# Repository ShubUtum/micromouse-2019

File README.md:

TODOs:

- [x] write a gitignore file
- [x] Timer Interrupt
- [x] PWM
- [x] UART TX, USB interface
- [x] Motor driver, H-Bridge interface
- [x] Motor Encoder 
- [x] PWM fix
- [x] ADC
- [ ] UART RX
- [ ] Schematic, routing
- [ ] PID controller
- [ ] moveing forward alignment & correction
- [ ] rotate left & right based on the POSCNT
- [ ] Map generation (maze discovery)
- [ ] finding shortest path to goal

- [ ] LED for measuring execution time
- [ ] UART, BT interface
- [ ] Visualization of UART data

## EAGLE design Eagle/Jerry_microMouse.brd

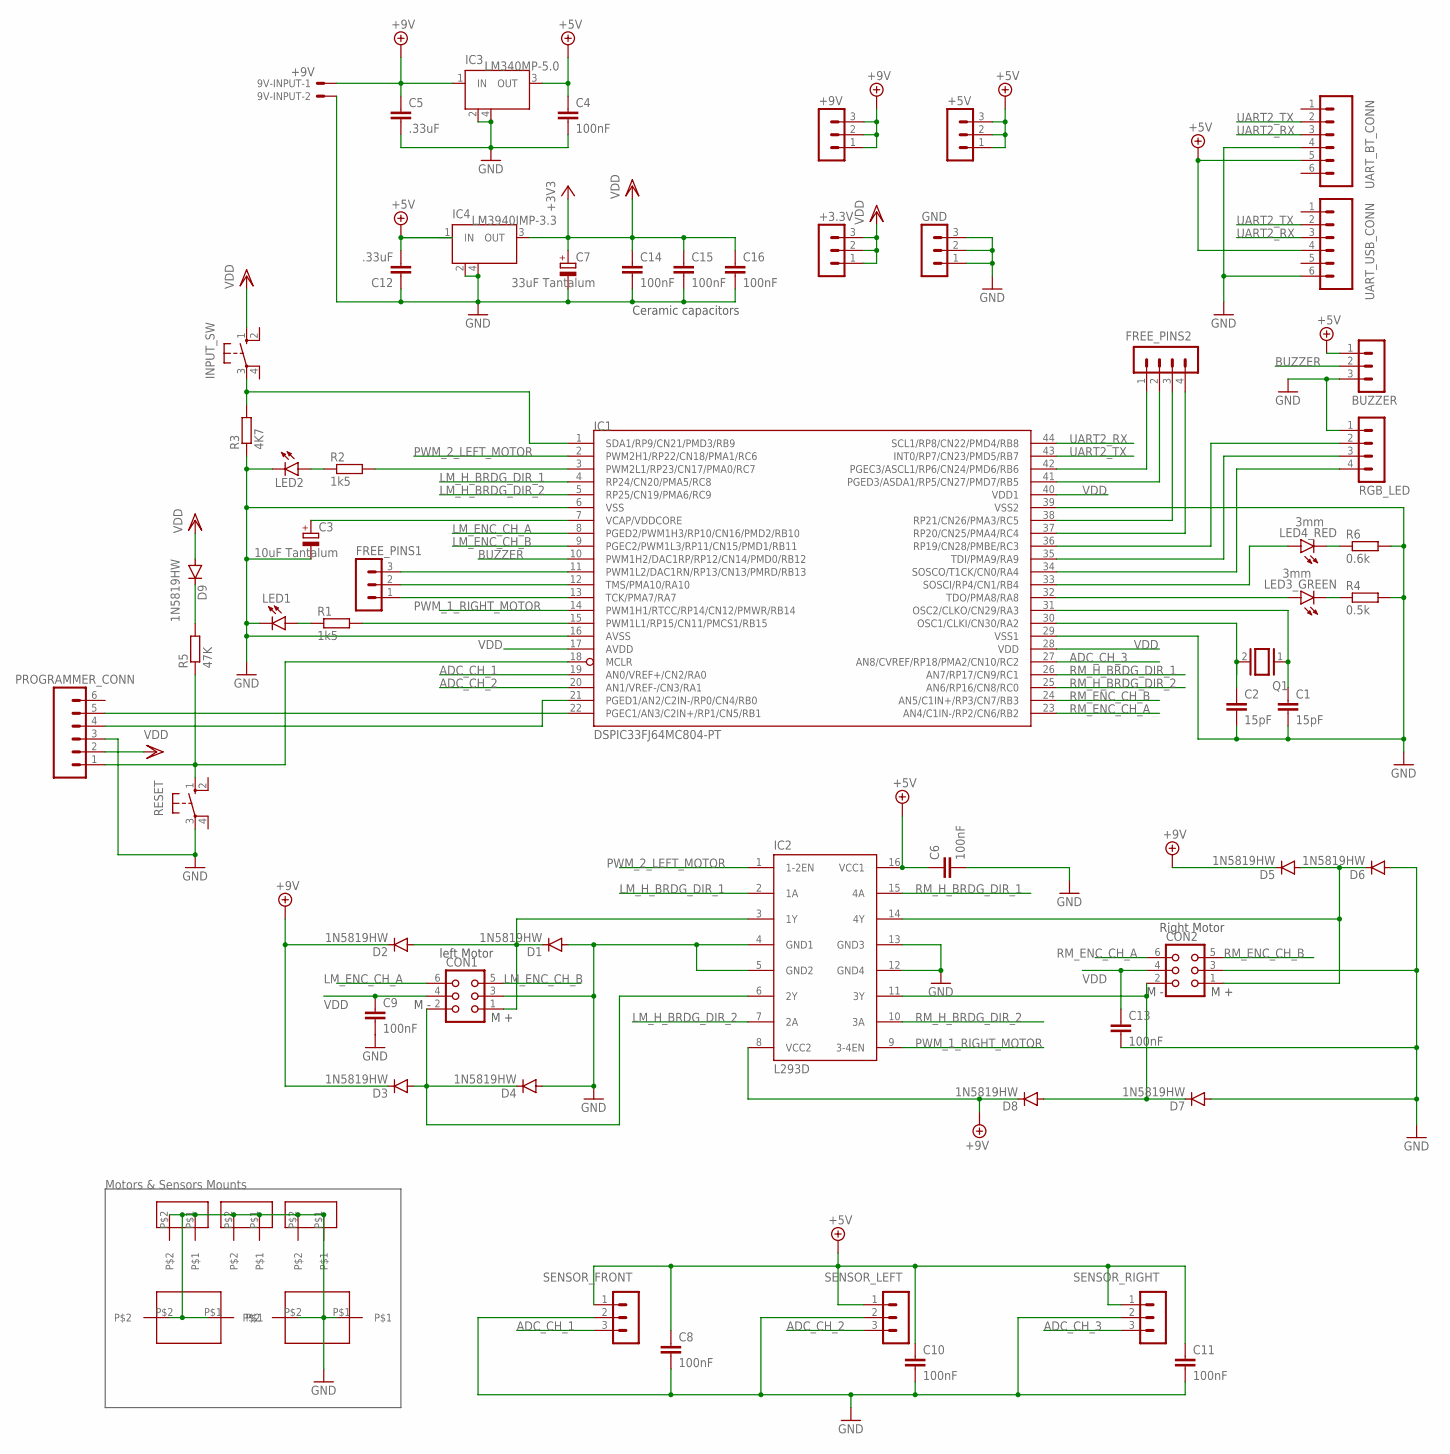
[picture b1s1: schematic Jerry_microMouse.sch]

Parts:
9V-INPUT: +9V; 22-23-2021
+3.3V, +5V, +9V: MA03-1
BUZZER: MA03-1
C1, C2: 15pF; C0805
C3: 10uF Tantalum; CT3216
C4, C6, C8, C9, C10, C11, C13, C14, C15, C16: 100nF; C0805
C5, C12: .33uF; C0805
C7: 33uF Tantalum; CT7343
CON1, CON2: CON06L
D1, D2, D3, D4, D5, D6, D7, D8, D9: 1N5819HW; SOD-123_MINI-SMA
FREE_PINS1: MA03-1
FREE_PINS2: MA04-1
GND: MA03-1
IC1: DSPIC33FJ64MC804-PT; TQFP44
IC2: L293D; DIL16
IC3: LM340MP-5.0; SOT223
IC4: LM3940IMP-3.3; SOT223
INPUT_SW: 10-XX; B3F-10XX
LED1, LED2: LED5MM
LED3_GREEN, LED4_RED: 3mm; Q62902-B155
PROGRAMMER_CONN: M06; 06P
Q1: XTAL/S; QS
R1, R2: 1k5; R0805
R3: 4K7; R0805
R4: 0.5k; R0805
R5: 47K; R0805
R6: 0.6k; R0805
RESET: 10-XX; B3F-10XX
RGB_LED: MA04-1
SENSOR_FRONT: MA03-1
SENSOR_LEFT: MA03-1
SENSOR_RIGHT: MA03-1
SENS_MNT_F: SENSOR_MOUNT_F; SENSOR_MOUNT
SENS_MNT_L: SENSOR_MOUNT_L; SENSOR_MOUNT
SENS_MNT_R: SENSOR_MOUNT_R; SENSOR_MOUNT
U$1, U$2: MOTOR_MOUNT
UART_BT_CONN: M06; 06P
UART_USB_CONN: M06; 06P

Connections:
+5V: +5V.1, +5V.2, +5V.3, BUZZER.1, C4.1, C6.1, C8.1, C10.1, C11.1, C12.2, IC2.16 (VCC1), IC3.3 (OUT), IC4.1 (IN), SENSOR_FRONT.1, SENSOR_LEFT.1, SENSOR_RIGHT.1, UART_BT_CONN.5, UART_USB_CONN.4
+9V: 9V-INPUT.1, +9V.1, +9V.2, +9V.3, C5.1, D2.C, D3.C, D5.C, D8.C, IC2.8 (VCC2), IC3.1 (IN)
ADC_CH_1: IC1.19 (AN0/VREF+/CN2/RA0), SENSOR_FRONT.3
ADC_CH_2: IC1.20 (AN1/VREF-/CN3/RA1), SENSOR_LEFT.3
ADC_CH_3: IC1.27 (AN8/CVREF/RP18/PMA2/CN10/RC2), SENSOR_RIGHT.3
BUZZER: BUZZER.2, IC1.10 (PWM1H2/DAC1RP/RP12/CN14/PMD0/RB12)
GND: 9V-INPUT.2, BUZZER.3, C1.2, C2.2, C3.-, C4.2, C5.2, C6.2, C7.-, C8.2, C9.2, C10.2, C11.2, C12.1, C13.2, C14.2, C15.2, C16.2, CON1.3, CON2.3, D1.A, D4.A, D6.A, D7.A, GND.1, GND.2, GND.3, IC1.6 (VSS), IC1.16 (AVSS), IC1.29 (VSS1), IC1.39 (VSS2), IC2.4 (GND1), IC2.5 (GND2), IC2.12 (GND4), IC2.13 (GND3), IC3.2 (GND), IC3.4 (GND), IC4.2 (GND), IC4.4 (GND), LED1.K (C), LED2.K (C), PROGRAMMER_CONN.3, R3.1, R4.2, R6.2, RESET.3, RGB_LED.1, SENSOR_FRONT.2, SENSOR_LEFT.2, SENSOR_RIGHT.2, SENS_MNT_F.P$1, SENS_MNT_F.P$2, SENS_MNT_L.P$1, SENS_MNT_L.P$2, SENS_MNT_R.P$1, SENS_MNT_R.P$2, U$1.P$1, U$1.P$2, U$2.P$1, U$2.P$2, UART_BT_CONN.4, UART_USB_CONN.6
LM_ENC_CH_A: CON1.6, IC1.8 (PGED2/PWM1H3/RP10/CN16/PMD2/RB10)
LM_ENC_CH_B: CON1.5, IC1.9 (PGEC2/PWM1L3/RP11/CN15/PMD1/RB11)
LM_H_BRDG_DIR_1: IC1.4 (RP24/CN20/PMA5/RC8), IC2.2 (1A)
LM_H_BRDG_DIR_2: IC1.5 (RP25/CN19/PMA6/RC9), IC2.7 (2A)
LM_M+: CON1.1, D1.C, D2.A, IC2.3 (1Y)
LM_M-: CON1.2, D3.A, D4.C, IC2.6 (2Y)
unnamed: IC1.3 (PWM2L1/RP23/CN17/PMA0/RC7), R2.2
unnamed: LED2.A, R2.1
unnamed: IC1.22 (PGEC1/AN3/C2IN+/RP1/CN5/RB1), PROGRAMMER_CONN.5
unnamed: IC1.1 (SDA1/RP9/CN21/PMD3/RB9), INPUT_SW.3, R3.2
unnamed: IC1.32 (TDO/PMA8/RA8), LED3_GREEN.A
unnamed: C2.1, IC1.30 (OSC1/CLKI/CN30/RA2), Q1.2
unnamed: C1.1, IC1.31 (OSC2/CLKO/CN29/RA3), Q1.1
unnamed: IC1.21 (PGED1/AN2/C2IN-/RP0/CN4/RB0), PROGRAMMER_CONN.4
unnamed: LED3_GREEN.K (C), R4.1
unnamed: IC1.15 (PWM1L1/RP15/CN11/PMCS1/RB15), R1.2
unnamed: IC1.33 (SOSCI/RP4/CN1/RB4), LED4_RED.A
unnamed: IC1.34 (SOSCO/T1CK/CN0/RA4), RGB_LED.4
unnamed: LED1.A, R1.1
unnamed: IC1.35 (TDI/PMA9/RA9), RGB_LED.3
unnamed: D9.C, R5.2
unnamed: IC1.36 (RP19/CN28/PMBE/RC3), RGB_LED.2
unnamed: FREE_PINS1.3, IC1.11 (PWM1L2/DAC1RN/RP13/CN13/PMRD/RB13)
unnamed: FREE_PINS2.1, IC1.42 (PGEC3/ASCL1/RP6/CN24/PMD6/RB6)
unnamed: FREE_PINS2.2, IC1.41 (PGED3/ASDA1/RP5/CN27/PMD7/RB5)
unnamed: FREE_PINS2.3, IC1.38 (RP21/CN26/PMA3/RC5)
unnamed: LED4_RED.K (C), R6.1
unnamed: FREE_PINS2.4, IC1.37 (RP20/CN25/PMA4/RC4)
unnamed: FREE_PINS1.2, IC1.12 (TMS/PMA10/RA10)
unnamed: FREE_PINS1.1, IC1.13 (TCK/PMA7/RA7)
PWM_1_RIGHT_MOTOR: IC1.14 (PWM1H1/RTCC/RP14/CN12/PMWR/RB14), IC2.9 (3-4EN)
PWM_2_LEFT_MOTOR: IC1.2 (PWM2H1/RP22/CN18/PMA1/RC6), IC2.1 (1-2EN)
RESET: IC1.18 (MCLR), PROGRAMMER_CONN.1, R5.1, RESET.1 (S)
RM_ENC_CH_A: CON2.6, IC1.23 (AN4/C1IN-/RP2/CN6/RB2)
RM_ENC_CH_B: CON2.5, IC1.24 (AN5/C1IN+/RP3/CN7/RB3)
RM_H_BRDG_DIR_1: IC1.26 (AN7/RP17/CN9/RC1), IC2.15 (4A)
RM_H_BRDG_DIR_2: IC1.25 (AN6/RP16/CN8/RC0), IC2.10 (3A)
RM_M+: CON2.1, D5.A, D6.C, IC2.14 (4Y)
RM_M-: CON2.2, D7.C, D8.A, IC2.11 (3Y)
UART2_RX: IC1.44 (SCL1/RP8/CN22/PMD4/RB8), UART_BT_CONN.3, UART_USB_CONN.3
UART2_TX: IC1.43 (INT0/RP7/CN23/PMD5/RB7), UART_BT_CONN.2, UART_USB_CONN.2
VCAP/VDDCORE: C3.+, IC1.7 (VCAP/VDDCORE)
VDD: +3.3V.1, +3.3V.2, +3.3V.3, C7.+, C9.1, C13.1, C14.1, C15.1, C16.1, CON1.4, CON2.4, D9.A, IC1.17 (AVDD), IC1.28 (VDD), IC1.40 (VDD1), IC4.3 (OUT), INPUT_SW.1 (S), PROGRAMMER_CONN.2

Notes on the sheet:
left Motor
Right Motor
M +
M -
Ceramic capacitors
Motors & Sensors Mounts

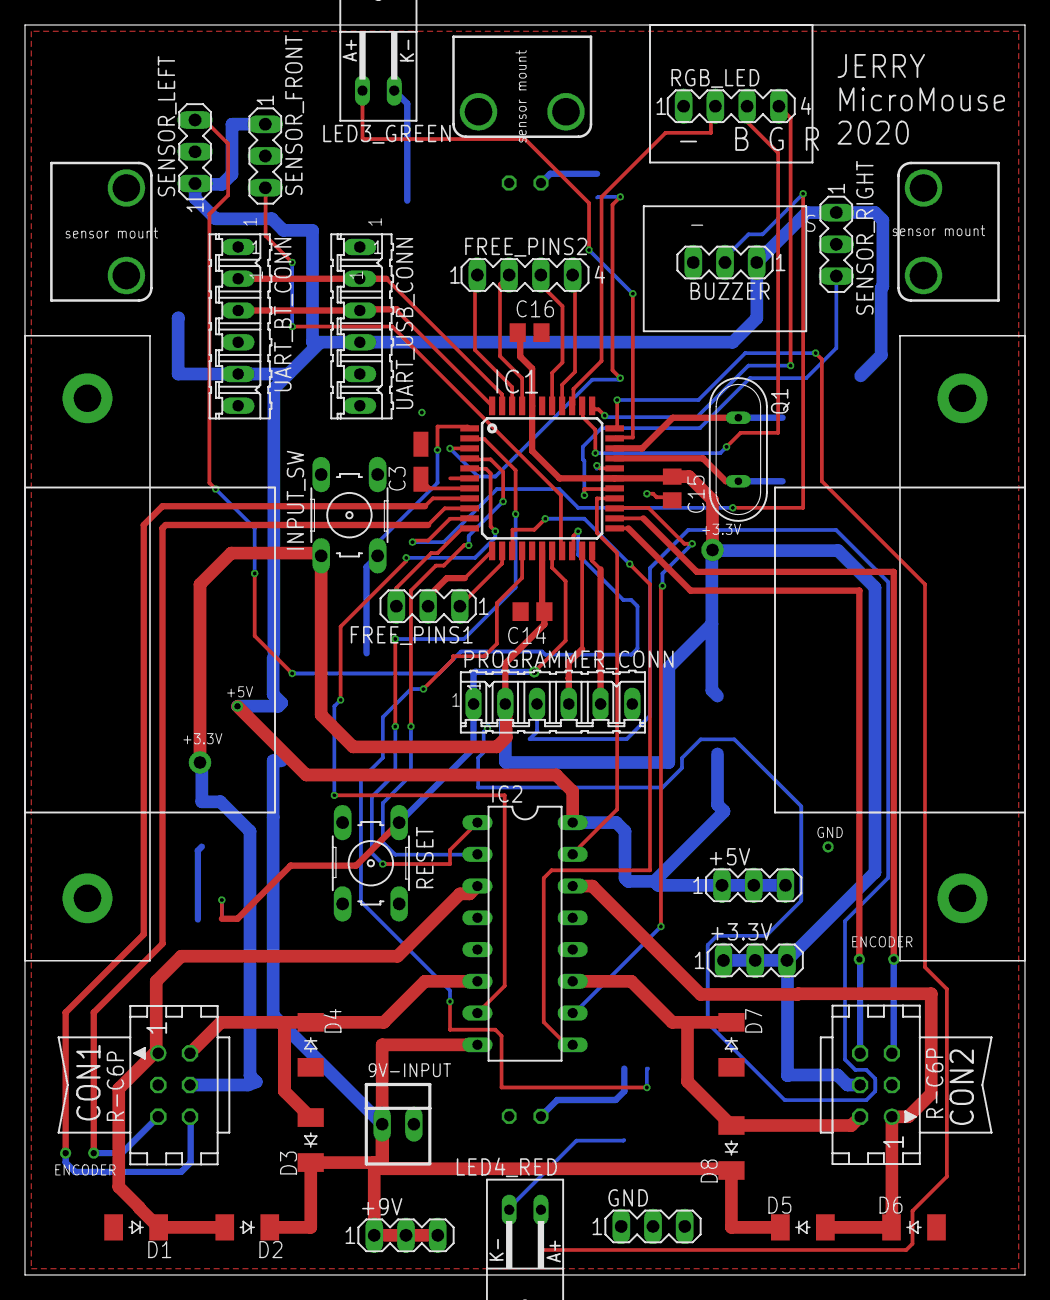
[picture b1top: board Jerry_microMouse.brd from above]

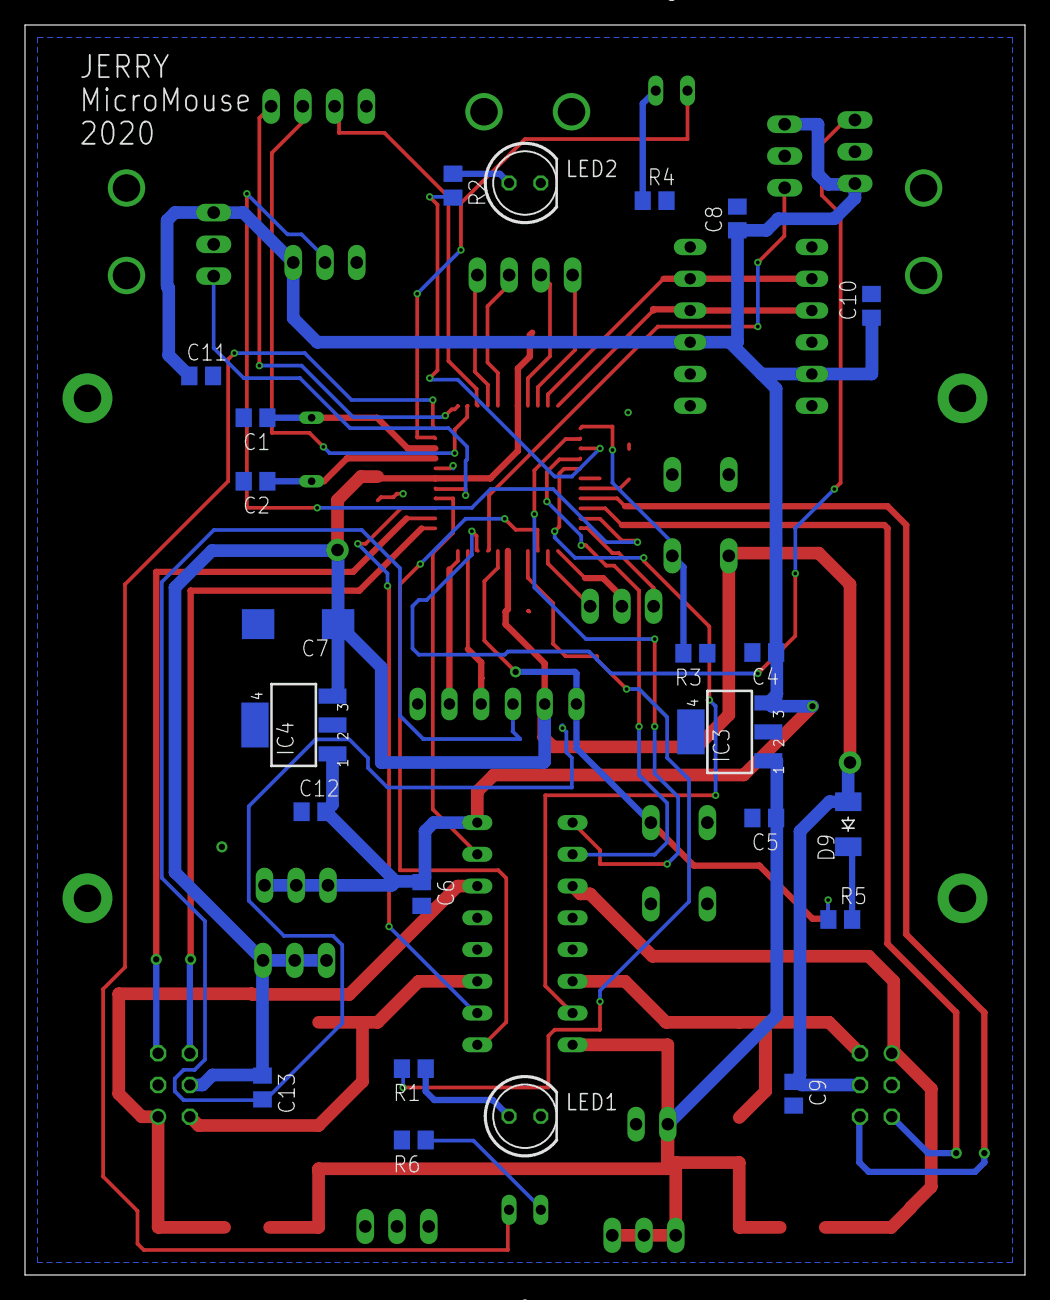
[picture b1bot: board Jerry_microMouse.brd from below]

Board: 2 copper layers, 80.0 x 100.0 mm, 64 parts (23 on the bottom side), 50 nets.

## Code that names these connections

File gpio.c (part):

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    __builtin_write_OSCCONL(OSCCON & 0xbf); // clear bit 6 (unlock, they are usually write protected)
    // inputs
     // input pin mapping example below:, here you choose the register with the device and assign an remappable pin
    RPINR14bits.QEA1R = 2; // QEI1 A to pin RB2
    RPINR14bits.QEB1R = 3; // QEI1 B to pin RB3
    RPINR16bits.QEA2R = 10; //QEI2 A to pin RB10
    RPINR16bits.QEB2R = 11; //QEI2 B to pin RB11
    
    RPINR19bits.U2RXR = 13; // input from uart to pin RB13
    //RPINR18bits.U1RXR = 1 ; //U1RX register is pin RB1 / RP1
    
    // outputs
    //output pin mapping example below, here you choose the pin register and then map it to a device 
    //RPOR6bits.RP12R = 0b00111; // pin RB12 to SPI1 miso (the cod 0b00111 idetifies SPI miso, table in datasheet)  
    //RPOR1bits.RP2R = 0b00011; // pin RP2 is connected to UART1 TX, for coding see table 11-2 in datasheet
    //end of set up of remappable pins
    
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    __builtin_write_OSCCONL(OSCCON & 0xbf); // clear bit 6 (unlock, they are usually write protected)
    // inputs
     // input pin mapping example below:, here you choose the register with the device and assign an remappable pin
    RPINR14bits.QEB1R = 10; // QEI1 B to pin RB10
    RPINR14bits.QEA1R = 11; // QEI1 A to pin RB11
    RPINR16bits.QEA2R = 2; //QEI2 A to pin RB2
    RPINR16bits.QEB2R = 3; //QEI2 B to pin RB3
    
    RPINR19bits.U2RXR = 8; // input from uart to pin RB8
    
    // outputs
    //output pin mapping example below, here you choose the pin register and then map it to a device 
    //RPOR6bits.RP12R = 0b00111; // pin RB12 to SPI1 miso (the cod 0b00111 idetifies SPI miso, table in datasheet)  
    //RPOR1bits.RP2R = 0b00011; // pin RP2 is connected to UART1 TX, for coding see table 11-2 in datasheet
    //end of set up of remappable pins
    
    RPOR3bits.RP7R = 0b00101;  // Map RB7 to U2TX UART2 Transmit
    
    RPOR6bits.RP12R  = 0; //default pin output for PWM2H1 RB12
    RPOR7bits.RP14R  = 0; //default pin output for PWM1H1 RB14
    RPOR11bits.RP22R = 0; //default pin output for PWM1H2 RC6
    
    RPOR12bits.RP24R = 0; //default pin output for H bridge LM dir control RC8
    RPOR12bits.RP25R = 0; //default pin output for H bridge LM dir control RC9
    RPOR8bits.RP16R  = 0; //default pin output for H bridge RM dir control RC0
    RPOR8bits.RP17R  = 0; //default pin output for H bridge RM dir control RC1
    
    RPOR7bits.RP15R  = 0; //default pin output for LED1 RB15 
    RPOR11bits.RP23R = 0; //default pin output for LED2 RC7
    //RPOR7bits.RPR  = 0; //default pin output for LED3 RA8
    RPOR2bits.RP4R   = 0; //default pin output for LED4 RB4
    RPOR9bits.RP19R  = 0; //default pin output for RGB LED RC3 (B)
    //RPOR7bits.RPR  = 0; //default pin output for RGB LED RA9 (G)
    //RPOR7bits.RPR  = 0; //default pin output for RGB LED RA4 (R)
    
    __builtin_write_OSCCONL(OSCCON | 0x40); // Lock PPS registers (lock again!)

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
    //outputs
    TRISBbits.TRISB14 =0; //PWM1H1 (RM))
    TRISBbits.TRISB12 =0; //PWM1H2 (Buzzer)
    TRISCbits.TRISC8  =0; //PWM2H1 (LM))

    TRISCbits.TRISC8  =0; //LM - H bridge dir control 1
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
    TRISAbits.TRISA8  =0; //Front GREEN LED3
    TRISBbits.TRISB4  =0; //Back RED LED4
    TRISBbits.TRISB15 =0; //LED1 RB15
    TRISCbits.TRISC7  =0; //LED2 RC7
    TRISCbits.TRISC3  =0; //LED RGB 2 RC3 (B)
    TRISAbits.TRISA9  =0; //LED RGB 3 RA9 (G)
    TRISAbits.TRISA4  =0; //LED RGB 4 RA4 (R)

    //for (i = 0; i < 40000; i++); // short delay ~ 1ms
}
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
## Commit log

2019-11-14 init project
2019-11-17 add PWM driver, and test it in main function
2019-11-26 [+] added motor perform function to control motor with h-bridge [untested]
2019-11-26 QEI (Encoder) module implemented
2019-11-26 Create README.md
    some todos
2019-11-27 qei fix
2019-11-27 [+] added uart function [UNTESTED]
2019-11-27 [~] fix bugged
2019-11-27 [~] update uart [TESTED]
2019-11-27 [~] moved some code into uart.h
2019-12-01 [+] added ADC conversion with interrupt [UNTESTED]
2019-12-02 fix PWM, adding ADC & DMA files, code organization
2019-12-04 [~] fixed control input direction bug
2019-12-04 [~] fixed poscnt bug, fixed uart sendString function, fixed h bridge pwm problem
2019-12-09 add PWM 1
2019-12-10 [+] added ADC with implemented DMA handler [UNTESTED]
2019-12-10 [~] adjusted data type conversion in DMA interrupt handler
2019-12-11 [+] added ADC + DMA [TESTED]
2019-12-12 adding the initial schematic diagram, update the task list in README
2019-12-16 UART receive functionality
2019-12-18 [incomplete] adding motor speed PI controller. organize Timer interrupt function
2019-12-18 [+] add schematic for H-bridge
2020-01-04 [+] added voltage regulator, reset switch, LEDs
2020-01-04 [~] clean up unused wire and component
2020-01-07 finish PID [untested] , finish schematic
2020-01-08 add UART socket to schematic, adjust Voltage reg
2020-01-10 recover PID code, add PID test code
2020-01-13 update schematic, finish placing components on board
2020-01-15 PCB signals routing
2020-01-19 add motor & sensor mounts, add GND planes
2020-01-22 remove memalloc
2020-01-28 adjust pi controller variable
2020-01-28 update PCB, manually routing
2020-01-29 moved motor mount from master to drivers branch
2020-01-29 motor mount and sensor mount
    closes #13 and closes #14
2020-03-01 - add pushButton.c, - update gpio with pin mappings for Jerry board, - add simple FSM (idle, search, navigate states) in fsm.c, - add RGB function to gpio.c, - add mouse move FW, BW, rotate left, rig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
2020-03-03 update configuration bits for dspic33fj128mc804
2020-03-05 disable watchdog, adding some delays
2020-03-05 Auto stash before merge of "drivers" and "origin/drivers"
2020-03-05 coordinate and maze representation
2020-03-07 maze solver implemented
2020-03-07 added just driving the shortest path without exploration
2020-03-11 switch clk source from internal to external HS crystal w PLL, all modules are working
2020-03-31 test mouse movement. move FW done
